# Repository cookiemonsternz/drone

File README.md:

# F<sub>~ish</sub>PV

_Tinywhoop drone with custom ESC, FC, and frame._

## What?

F<sub>\~ish</sub>PV is a open source, custom stack, 75mm tinywhoop drone design.
It utilises AM32 for the ESC firmware and Betaflight for the flight controller. 

Custom components include a from-scratch frame, designed for 3d printing (in HP-12-CF filament), a fully custom 15A ESC, and a custom FC. 

**The ESC:**
- 15A Continuous
- 20A Peak for 5s (unverified :O)
- 2S Battery (only)
- AM32 Firmware
- DSHOT Communication + Voltage telemetry
- Current Sense
  
**The FC:**
- STM32F405
- OSD: MAX7456
- IMU: ICM-42688-P
- 128Mbit blackbox
- USB DFU
- 2S Battery (only)
- BEC: 5V/0.5A Max
- Mounting: 25.5x25.5
- Dimensions: 28.3x28.3x10
- UART: 1, 4, 5
- Buzzer!

## Why?

To be honest a lot of this project was just for my own learning, but I also wanted to make a drone that could be generally cheaper than buying prebuilt components. I've somewhat achieved this, with a net cost of ~$300 USD, but obviously this cost is higher due to lack of bulk pricing. Unfortunately, some parts I wanted to design from scratch proved to be infeasible within the scope of this project (namely vtx and vrx) so that has driven the total cost up slightly.

Aside from that, drones are cool, and tinywhoops especially so. The main benefit in my opinion is the crashability. The size makes it much more feasible to use alternative manufacturing options. As I mentioned earlier, I designed this with HP-12-CF filament in mind, but HP-12 MJF Nylon is also a very feasible option that could potentially be quite durable (I have simulated both, but it is worth noting that the CF simulations will not be entirely accurate due to the weakness along layer lines not being modelled).

## How to use?

The drone assembly should be reasonably straightforward, I have provided a wonderful exploded diagram that should help significantly:

Feel free to assemble it how you see fit, I'll likely change some things in the future but I'd like to try this configuration for now.

For wiring, theres this handy diagram. A lot of it just uses jst-sh connectors (as conformant to the [Betaflight Connector Standard](https://betaflight.com/docs/development/manufacturer/connector-standard)).

The ELRS receiver and vtx module can be attached however you see fit. I have included a mounting plate, and myself intend to use hot glue but velcro, etc. are also options.

Aside from the physical assembly, the FC and ESC must be flashed as outlined below or in the respective folders in **firmware/**. As I didn't want to do a bunch of pull requests for a likely one off design, I have provided compiled versions of the firmware. If you want to compile yourself, check out my forks of [Betaflight](https://github.com/cookiemonsternz/betaflight) and [AM32](https://github.com/cookiemonsternz/AM32). AM32 was built using github actions, and Betaflight was built locally using WSL as outlined in [the documentation](https://betaflight.com/docs/development#development).

### ESC Firmware

The esc runs on AM32, an open source ESC firmware which manages motor control, communication via dshot, and telemetry.

#### Bootloader

First of all, we need to install the bootloader onto each of the chips. For each chip, connect via the exposed swd/io interface, as outlined in the following table, and flash the bootloader hex file from **firmware/esc/bootloader/**

| MCU | SWDIO | SWDCLK |
|-----|-------|--------|
| 1   | TP1   | TP2    |
| 2   | TP3   | TP4    |
| 3   | TP6   | TP5    |
| 4   | TP8   | TP7    |

#### Firmware

Next connect the flight controller (which should be flashed before this step),
visit [am32 configurator](https://am32.ca/) and upload the firmware from **firmware/esc/**

---

### FC Firmware

Installation follows the same procedure as pretty much any flight controller.
Visit [Betaflight Configurator](https://app.betaflight.com/) and select firmware flasher. 

At the bottom of the screen, press load local:

Upload the hex file and then hit flash!

That's it, should be all configured (maybe) but I'd reccomend going through and doing the regular adjustments and calibration.

## Renders

## Zine Page

## Simulations

I ran a handful of simulations in FreeCAD, and these are just a small sample of the results I got. 

First up, a collision where the battery is impacted. Think the drone just dropping onto the ground. This is for a collision at approximately 50km/h assuming a collision time of 25ms and a net mass of around 250g (so probably a bit extreme), to be specific, I modelled a force of 150N.

As you can see, there is even deflection across all four mounting posts for the FC/ESC stack, which will result in minimal tensile strain on the PCBs (which is the typical cause of damage).

Another type of collision I modelled is just a collision directly to the prop guards. Again, a 150N force which would be ~50km/h as mentioned above.

There is a lot of displacement on the prop guard but it is effectively dissipated and won't have much impact on the electronics, which is the main thing to be worried about. 
For this specific impact, I would be reasonably worried about damage to the frame, but for most crashes (which are probably not at 50km/h) it should be perfectly fine.

Many more simulations at different loads and also modelling the HP-12 MJF material can be found [here](https://github.com/cookiemonsternz/drone/blob/main/journals/journal-14-05-2026.md).

## BOM

| Desc                               | Value              | Package        | Link                                                                                        | Num | Needed | MOQ | MOQ Price | Net Price | Running Total |
|------------------------------------|--------------------|----------------|---------------------------------------------------------------------------------------------|-----|--------|-----|-----------|-----------|---------------|
| **Capacitors**                         |                    |                |                                                                                             |     |        |     |           |           |               |
| 10nF Ceramic Cap, 0402             | 10nF               | 0402           | https://www.lcsc.com/product-detail/C15195.html                                             | 1   | 1      | 100 | $0.16     | $0.16     | $0.16         |
| 22nF Ceramic Cap, 0402             | 22nF               | 0402           | https://www.lcsc.com/product-detail/C1532.html                                              | 2   | 2      | 100 | $0.21     | $0.21     | $0.37         |
| 100nF Ceramic Cap, 0402            | 100nF              | 0402           | https://www.lcsc.com/product-detail/C1525.html                                              | 44  | 44     | 100 | $0.15     | $0.15     | $0.52         |
| 1uF Ceramic Cap, 0402              | 1uF                | 0402           | https://www.lcsc.com/product-detail/C52923.html                                             | 4   | 4      | 100 | $0.4      | $0.40     | $0.92         |
| 2.2uF Ceramic Cap, 0402            | 2.2uF              | 0402           | https://www.lcsc.com/product-detail/C12530.html                                             | 3   | 3      | 100 | $0.32     | $0.32     | $1.24         |
| 4.7uF Capacitors, 0603             | 4.7uF              | 0603           | https://www.lcsc.com/product-detail/C19666.html                                             | 4   | 4      | 10  | $0.11     | $0.11     | $1.35         |
| 22uF Capacitors, 0603              | 22uF               | 0603           | https://www.lcsc.com/product-detail/C86295.html                                             | 4   | 4      | 10  | $0.16     | $0.16     | $1.51         |
| 22uF Capacitors, 0805              | 22uF               | 0805           | https://www.lcsc.com/product-detail/C29277.html                                             | 2   | 2      | 10  | $0.21     | $0.21     | $1.72         |
| 22uF Electrolytic Cap, SMD         | 22uF               | SMD,D4xL5.4mm  | https://www.lcsc.com/product-detail/C335975.html                                            | 2   | 2      | 20  | $0.48     | $0.48     | $2.20         |
| 47uF Electrolytic Cap, SMD         | 47uF               | SMD,D4xL5.4mm  | https://www.lcsc.com/product-detail/C87853.html                                             | 2   | 2      | 20  | $0.53     | $0.53     | $2.73         |
| **Resistors**                          |                    |                |                                                                                             |     |        |     |           |           |               |
| 22R Resistors, 0402                | 22r                | 0402           | https://www.lcsc.com/product-detail/C2906914.html                                           | 26  | 26     | 100 | $0.07     | $0.07     | $2.80         |
| 75R Resistor, 0402                 | 75?                | 0402           | https://www.lcsc.com/product-detail/C25133.html                                             | 4   | 4      | 100 | $0.09     | $0.09     | $2.89         |
| 1k Resistor, 0402                  | 1k?                | 0402           | https://www.lcsc.com/product-detail/C11702.html                                             | 17  | 17     | 100 | $0.11     | $0.11     | $3.00         |
| 2.2k Resistor, 0402                | 2.2k?              | 0402           | https://www.lcsc.com/product-detail/C25879.html                                             | 3   | 3      | 100 | $0.10     | $0.10     | $3.10         |
| 10k Resistor, 0402                 | 10k?               | 0402           | https://www.lcsc.com/product-detail/C25744.html                                             | 6   | 6      | 100 | $0.13     | $0.13     | $3.23         |
| 100k Resistor, 0402                | 100k?              | 0402           | https://www.lcsc.com/product-detail/C25741.html                                             | 4   | 4      | 100 | $0.09     | $0.09     | $3.32         |
| 10k Resistor Arrays, 0603x4        | 10k                | 0603x4         | https://www.lcsc.com/product-detail/C110924.html                                            | 6   | 6      | 50  | $0.55     | $0.55     | $3.87         |
| 124k Voltage Div Resistor, 0603    | 124k               | 0603           | https://www.lcsc.com/product-detail/C2933136.html                                           | 1   | 1      | 100 | $0.11     | $0.11     | $3.98         |
| 0.5m Shunt Resistor, 1216          | 0.5mr              | 1216           | https://www.lcsc.com/product-detail/C2688874.html                                           | 1   | 1      | 1   | $1.01     | $1.01     | $4.99         |
| **Diodes**                             |                    |                |                                                                                             |     |        |     |           |           |               |
| Red LED                            |                    | 0603           | https://www.lcsc.com/product-detail/C51933292.html                                          | 1   | 1      | 50  | $0.13     | $0.13     | $5.12         |
| Blue LED                           |                    | 0603           | https://www.lcsc.com/product-detail/C2288.html                                              | 1   | 1      | 50  | $0.51     | $0.51     | $5.63         |
| Green LED                          |                    | 0603           | https://www.lcsc.com/product-detail/C22371297.html                                          | 1   | 1      | 50  | $0.71     | $0.71     | $6.34         |
| Schottky Diode                     |                    | SOD-323        | https://www.lcsc.com/product-detail/C191023.html                                            | 2   | 2      | 50  | $0.54     | $0.54     | $6.88         |
| **Connectors**                         |                    |                |                                                                                             |     |        |     |           |           |               |
| Camera Conn                        | 3P SH              | SMD,P=1mm      | https://www.lcsc.com/product-detail/C7430452.html                                           | 1   | 1      | 5   | $0.34     | $0.34     | $7.22         |
| UART Conns                         | 4P SH              | SMD,P=1mm      | https://www.lcsc.com/product-detail/C7433440.html                                           | 3   | 3      | 10  | $0.35     | $0.35     | $7.57         |
| VTX Conn                           | 5P SH              | SMD,P=1mm      | https://www.lcsc.com/product-detail/C2845373.html                                           | 1   | 1      | 5   | $0.58     | $0.58     | $8.15         |
| ESC Conns                          | 8P SH              | SMD,P=1mm      | https://www.lcsc.com/product-detail/C2764202.html                                           | 2   | 2      | 5   | $0.61     | $0.61     | $8.76         |
| USB Micro B Conn                   |                    | SMD            | https://www.lcsc.com/product-detail/C404969.html                                            | 1   | 1      | 10  | $0.41     | $0.41     | $9.17         |
| **FC**                                 |                    |                |                                                                                             |     |        |     |           |           |               |
| STM32F405 (U1)                     |                    | LQFP-64(10x10) | https://www.lcsc.com/product-detail/C15742.html                                             | 1   | 1      | 1   | $3.93     | $3.93     | $13.10        |
| ICM-42668-P : IMU (U2)             |                    | LGA-14(2.5x3)  | https://www.lcsc.com/product-detail/C1850418.html                                           | 1   | 1      | 1   | $12.88    | $12.88    | $25.98        |
| MAX-7456eui+ (U3)                  | Source: Aliexpress |                | https://www.aliexpress.com/item/33005990891.html                                            | 1   | 1      | 1   | $4.28     | $4.28     | $30.26        |
| BL8072CLTR-3.3 (3.3V LDO) (U6)     | 3.3V               | SOT-223-3      | https://www.lcsc.com/product-detail/C843780.html                                            | 1   | 1      | 5   | $0.99     | $0.99     | $31.25        |
| SGM2212-3.3XKC3G/TR (IMU LDO) (U7) | 3.3V               | SOT-223-3      | https://www.lcsc.com/product-detail/C3294699.html                                           | 1   | 1      | 1   | $0.61     | $0.61     | $31.86        |
| W25Q128JVSIQ TR (Flash) (U8)       |                    | SOIC-8-208mil  | https://www.lcsc.com/product-detail/C97521.html                                             | 1   | 1      | 1   | $2.32     | $2.32     | $34.18        |
| TPS62173DSG (5V BEC) (U4, U5)      | 5V                 | WSON-8-EP(2x2) | https://www.lcsc.com/product-detail/C181384.html                                            | 2   | 2      | 1   | $0.93     | $1.86     | $36.04        |
| BMP280 Baro (U10)                  |                    | LGA-8(2x2.5)   | https://www.lcsc.com/product-detail/C83291.html                                             | 1   | 1      | 1   | $6.90     | $6.90     | $42.94        |
| 27MHz Crystal (Y1)                 | 27MHz              | SMD3225-4P     | https://www.lcsc.com/product-detail/C9008.html                                              | 1   | 1      | 10  | $0.77     | $0.77     | $43.71        |
| 8MHz Crystal w/ Caps (Y2)          | 8MHz               | SMD3213-3P     | https://www.lcsc.com/product-detail/C907975.html                                            | 1   | 1      | 5   | $1.05     | $1.05     | $44.76        |
| BEC Inductors (L1, L2)             | 2.2uH              | 0806           | https://www.lcsc.com/product-detail/C695610.html                                            | 1   | 1      | 5   | $0.82     | $0.82     | $45.58        |
| BOOT Button (SW2)                  |                    | SMD,4x3mm      | https://www.lcsc.com/product-detail/C720477.html                                            | 1   | 1      | 10  | $0.54     | $0.54     | $46.12        |
| Reverse Pol. Mosfet (Q1)           |                    | SOT-23         | https://www.lcsc.com/product-detail/C15127.html                                             | 1   | 1      | 10  | $0.59     | $0.59     | $46.71        |
| **ESC**                                |                    |                |                                                                                             |     |        |     |           |           |               |
| 470nH Inductor, 0603               | 470nH              | 0603           | https://www.lcsc.com/product-detail/C113132.html                                            | 1   | 1      | 10  | $0.47     | $0.47     | $47.18        |
| Mosfets (SP40N03GNJ)               |                    | PDFN-8L(3x3)   | https://www.lcsc.com/product-detail/C22466709.html                                          | 24  | 24     | 5   | $1.05     | $5.25     | $52.43        |
| ESC MCUs (AT32F421G8U7)            |                    | QFN-28-EP(4x4) | https://www.lcsc.com/product-detail/C2765098.html                                           | 4   | 4      | 1   | $0.85     | $3.40     | $55.83        |
| ESC Mosfet Gate Drivers (NSG2065Q) |                    | QFN-24-EP(4x4) | https://www.lcsc.com/product-detail/C41414478.html                                          | 4   | 4      | 1   | $0.48     | $1.92     | $57.75        |
| Current Sense Amplifier (INA180B2) |                    | SOT-23-5       | https://www.lcsc.com/product-detail/C2057844.html                                           | 1   | 1      | 1   | $0.26     | $0.26     | $58.01        |
| 8V Regulator (LMR51420YDDCR)       |                    | SOT-23-6       | https://www.lcsc.com/product-detail/C5383002.html                                           | 1   | 1      | 1   | $0.83     | $0.83     | $58.84        |
| 3.3V Regulator (TLV76733DRVR)      |                    | WSON-6(2x2)    | https://www.lcsc.com/product-detail/C2848334.html                                           | 1   | 1      | 5   | $1.01     | $1.01     | $59.85        |
| **BOARDS**                             |                    |                |                                                                                             |     |        |     |           |           | $59.85        |
| ESC Board + Stencil (JLCPCB)       |                    |                |                                                                                             |     |        |     |           | $5.29     | $65.14        |
| FC Board + Stencil (JLCPCB)        |                    |                |                                                                                             |     |        |     |           | $5.21     | $70.35        |
| Frame (JLC3DP, HP-12-CF)           |                    |                |                                                                                             |     |        |     |           | $5.56     | $75.91        |
| **MODULES**                            |                    |                |                                                                                             |     |        |     |           |           | $75.91        |
| ELRS Receiver (RP1 Nano Clone)     |                    |                | https://www.aliexpress.com/item/1005005236594556.html                                       | 1   | 1      | 1   | $12.62    | $12.62    | $88.53        |
| CaddX Ant Camera                   |                    |                | https://www.aliexpress.com/item/1005008798090166.html                                       | 1   | 0      | 1   | $12.99    | $0.00     | $88.53        |
| PandaRC Nano25 VTX                 |                    |                | https://www.aliexpress.com/item/1005011701933149.html                                       | 1   | 0      | 1   | $18.94    | $0.00     | $88.53        |
| Happymodel RS1102 13500KV Motors   |                    |                | https://kiwiquads.co.nz/product/happymodel-rs1102-kv13500-brushless-motor-for-m8-freestyle/ | 4   | 4      | 4   | $11.11    | $44.44    | $132.97       |
| 40mm 1.5mm Shaft Triblade Props    |                    |                | https://www.aliexpress.com/item/1005010520091463.html                                       | 4   | 4      | 16  | $6.37     | $6.37     | $139.34       |
| 2s 680mah lipo                     |                    |                | https://kiwiquads.co.nz/product/betafpv-lava-series-ii-2s-680mah-95c/                       | 1   | 1      | 1   | $14.62    | $14.62    | $153.96       |
| Radiomaster T8L                    |                    |                | https://radiomasterrc.com/products/t8l-radio-controller?variant=47089026465984              | 1   | 1      | 1   | $34.99    | $34.99    | $188.95       |
| TS832 Receiver                     |                    |                | https://www.aliexpress.com/item/1005012037139433.html                                       | 1   | 0      | 1   | $43.86    | $0.00     | $188.95       |

| Totals (EXCL. VIDEO SYSTEM) |         |             |
|-----------------------------|---------|-------------|
| Vendor                      | Net     | W/ Shipping |
| JLCPCB / 3DP                | $16.06  | $41.99      |
| LCSC                        | $55.16  | $55.55      |
| Aliexpress                  | $23.27  | $22.95      |
| Kiwiquads                   | $59.05  | $61.96      |
| Radiomaster                 | $34.99  | $44.99      |
| JLCPCB                      | $10.50  | $32.06      |
| ---                         | $199.03 | $259.50     |

## Cad Links

All of the CAD source files can be found on [Onshape](https://cad.onshape.com/documents/5b69b7ad5dc2bcb1a562cae6/w/28cfd389aaff8b3000581458/e/21531bda6c88e5e5db7731e6?configuration=List_q74UD91e5eSlmt%3DDefault&renderMode=0&uiState=6a005b50d3c7c0f6100b1ec5). 
The physics simulations can be found in the FreeCAD project under **hardware/cad/sim/**

## Directory Structure

- **firmware/**
  - **esc/** - ESC Firmware (AM32)
  - **fc/** - FC Firmware (Betaflight)
- **hardware/**
    - **bom/** - BOM Files (CSV and LibreOffice Calc)
    - **cad/** - CAD Files
      - **render/** - Files for rendering (inc. gltf models) *Note that the Blender file for the renders exceeds the maximum file size for Github, it can be found in [Google Drive](https://drive.google.com/file/d/1S7Jwgq-ZpHFBb5yz26d0MQlCH4Twi4XQ/view?usp=sharing).*
      - **sim/** - FreeCAD files for FEM Analysis
    - **esc/** - ESC KiCad Project
      - **production/** - Production files (Gerber, etc.)
    - **fc/** - FC KiCad Project
      - **production/** - Production files (Gerber, etc.)
    - **lib/** - Shared KiCad libraries
    - **wiring-diagram/** - Wiring diagram
- **journals/**
- **zine/** - Zine page :)

## References
[Betaflight Documentation](https://betaflight.com/docs/development)

[AM32 Documentation](https://wiki.am32.ca/general/docs.html) - Especially re [Hardware Design](https://wiki.am32.ca/development/Hardware-Design.html)

[AcciFPV FC](https://www.pcbway.com/project/shareproject/Acci_FPV_Flight_Controller_Betaflight_STM32F405_AT32F435_48fb0ecb.html)

[Hack Club Blueprint - FC Guided Project](https://blueprint.hackclub.com/starter-projects/flightcontroller)

[JustFPV ESC Design](https://www.youtube.com/watch?v=TwAmmPxOpTM)

AM32 & Betaflight Discords

And various others which I have forgotten.

#### This project was created for [Hack Club](https://hackclub.com/) - [Fallout](https://fallout.hackclub.com/)

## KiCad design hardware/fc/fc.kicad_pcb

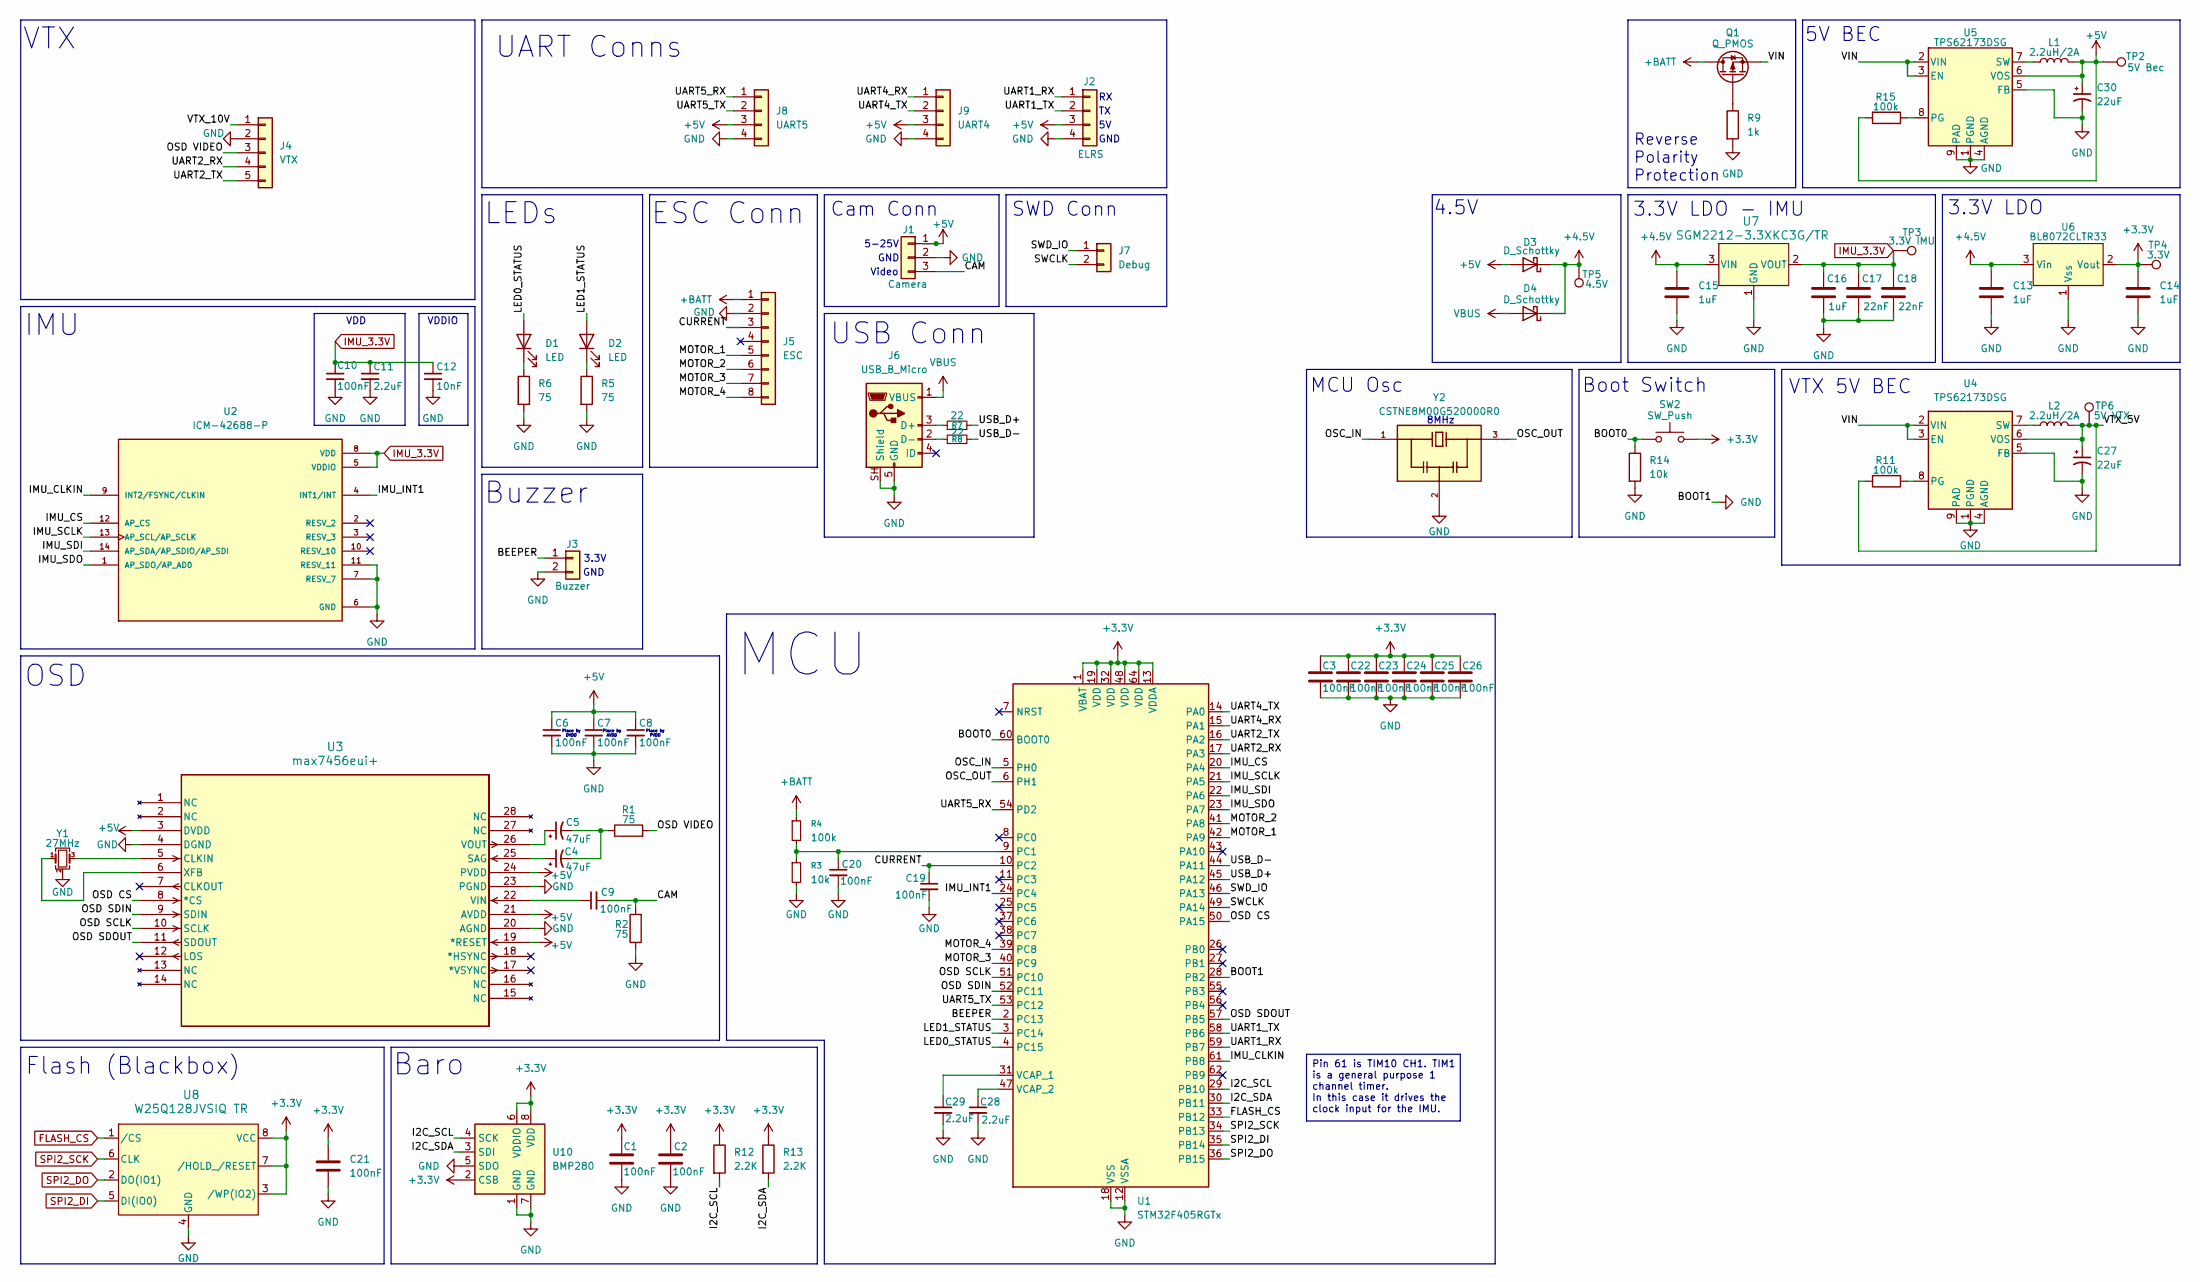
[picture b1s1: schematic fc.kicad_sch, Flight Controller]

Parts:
C1, C2, C3, C6, C7, C8, C9, C10, C19, C20, C21, C22, C23, C24, C25, C26: 100nF; C_0402_1005Metric
C4, C5: 47uF; CP_Elec_4x5.4
C11, C28, C29: 2.2uF; C_0402_1005Metric
C12: 10nF; C_0402_1005Metric
C13, C14, C15, C16: 1uF; C_0402_1005Metric
C17, C18: 22nF; C_0402_1005Metric
C27, C30: 22uF; CP_Elec_4x5.4
D1, D2: LED; LED_0603_1608Metric
D3, D4: D_Schottky; D_SOD-323
J1: Camera; JST_SH_BM03B-SRSS-TB_1x03-1MP_P1.00mm_Vertical
J2: ELRS; JST_SH_BM04B-SRSS-TB_1x04-1MP_P1.00mm_Vertical
J3: Buzzer; SolderWire-0.1sqmm_1x02_P3.6mm_D0.4mm_OD1mm
J4: VTX; JST_SH_BM05B-SRSS-TB_1x05-1MP_P1.00mm_Vertical
J5: ESC; JST_SH_BM08B-SRSS-TB_1x08-1MP_P1.00mm_Vertical
J6: USB_B_Micro; SHOUHAN_MICROXNJ
J7: Debug; SolderWire-0.1sqmm_1x02_P3.6mm_D0.4mm_OD1mm
J8: UART5; JST_SH_BM04B-SRSS-TB_1x04-1MP_P1.00mm_Vertical
J9: UART4; JST_SH_BM04B-SRSS-TB_1x04-1MP_P1.00mm_Vertical
L1, L2: 2.2uH/2A; INDC1608X95N
Q1: Q_PMOS; SOT-23
R1, R2, R5, R6: 75; R_0402_1005Metric
R3, R14: 10k; R_0402_1005Metric
R4, R11, R15: 100k; R_0402_1005Metric
R7, R8: 22; R_0402_1005Metric
R9: 1k; R_0402_1005Metric
R12, R13: 2.2K; R_0402_1005Metric
SW2: SW_Push; SW_TS-1088-AR02016
TP2: 5V Bec; TestPoint_Pad_D1.0mm
TP3: 3.3V IMU; TestPoint_Pad_D1.0mm
TP4: 3.3V; TestPoint_Pad_D1.0mm
TP5: 4.5V; TestPoint_Pad_D1.0mm
TP6: 5V VTX; TestPoint_Pad_D1.0mm
U1: STM32F405RGTx; LQFP-64_10x10mm_P0.5mm
U2: ICM-42688-P; PQFN50P300X250X97-14N; PARTREV 1.2
U3: max7456eui+; 21-0108G_U28E-5_MXM
U4, U5: TPS62173DSG; WSON-8-1EP_2x2mm_P0.5mm_EP0.9x1.6mm_ThermalVias
U6: BL8072CLTR33; SOT-223-3_TabPin2
U7: SGM2212-3.3XKC3G/TR; SOT-223-3_TabPin2
U8: W25Q128JVSIQ TR; SOIC_208MIL_WIN
U10: BMP280; Bosch_LGA-8_2x2.5mm_P0.65mm_ClockwisePinNumbering
Y1: 27MHz; Crystal_SMD_3225-4Pin_3.2x2.5mm
Y2: CSTNE8M00G520000R0; OSC_CSTNE8M00G520000R0; PARTREV JGC42-8858A

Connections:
+3.3V: C1.1, C2.1, C3.1, C14.1, C21.1, C22.1, C23.1, C24.1, C25.1, C26.1, R12.1, R13.1, SW2.2, TP4.1, U1.1 (VBAT), U1.13 (VDDA), U1.19 (VDD), U1.32 (VDD), U1.48 (VDD), U1.64 (VDD), U6.2 (Vout), U8.3 (/WP(IO2)), U8.7 (/HOLD_/RESET), U8.8 (VCC), U10.2 (CSB), U10.6 (VDDIO), U10.8 (VDD); also elsewhere on the board
+4.5V: C13.1, C15.1, D3.1 (K), D4.1 (K), TP5.1 (1_1), U6.3 (Vin), U7.3 (VIN)
+5V: C6.1, C7.1, C8.1, C30.1, D3.2 (A), J1.1, J2.3, J8.3, J9.3, L1.2, R15.2, TP2.1, U3.3 (DVDD), U3.19 (*RESET), U3.21 (AVDD), U3.24 (PVDD), U5.6 (VOS); also elsewhere on the board
+BATT: J5.1, Q1.D, R4.1
/BEEPER: J3.1, U1.2 (PC13)
/BOOT0: R14.1, SW2.1, U1.60 (BOOT0)
/CAM: C9.2, J1.3, R2.2
/CURRENT: C19.1, J5.3, U1.10 (PC2)
/I2C_SCL: R12.2, U1.29 (PB10), U10.4 (SCK)
/I2C_SDA: R13.2, U1.30 (PB11), U10.3 (SDI)
/IMU_CLKIN: U1.61 (PB8), U2.9 (INT2/FSYNC/CLKIN)
/IMU_CS: U1.20 (PA4), U2.12 (AP_CS)
/IMU_INT1: U1.24 (PC4), U2.4 (INT1/INT)
/IMU_SCLK: U1.21 (PA5), U2.13 (AP_SCL/AP_SCLK)
/IMU_SDI: U1.22 (PA6), U2.14 (AP_SDA/AP_SDIO/AP_SDI)
/IMU_SDO: U1.23 (PA7), U2.1 (AP_SDO/AP_AD0)
/LED0_STATUS: D1.2 (A), U1.4 (PC15)
/LED1_STATUS: D2.2 (A), U1.3 (PC14)
/MOTOR_1: J5.5, U1.42 (PA9)
/MOTOR_2: J5.6, U1.41 (PA8)
/MOTOR_3: J5.7, U1.40 (PC9)
/MOTOR_4: J5.8, U1.39 (PC8)
/OSC_IN: U1.5 (PH0), Y2.1
/OSC_OUT: U1.6 (PH1), Y2.3
/OSD CS: U1.50 (PA15), U3.8 (*CS)
/OSD SCLK: U1.51 (PC10), U3.10 (SCLK)
/OSD SDIN: U1.52 (PC11), U3.9 (SDIN)
/OSD SDOUT: U1.57 (PB5), U3.11 (SDOUT)
/OSD VIDEO: J4.3, R1.2
/SWCLK: J7.2, U1.49 (PA14)
/SWD_IO: J7.1, U1.46 (PA13)
/UART1_RX: J2.1, U1.59 (PB7)
/UART1_TX: J2.2, U1.58 (PB6)
/UART2_RX: J4.4, U1.17 (PA3)
/UART2_TX: J4.5, U1.16 (PA2)
/UART4_RX: J9.1, U1.15 (PA1)
/UART4_TX: J9.2, U1.14 (PA0)
/UART5_RX: J8.1, U1.54 (PD2)
/UART5_TX: J8.2, U1.53 (PC12)
/USB_D+: R7.2, U1.45 (PA12)
/USB_D-: R8.2, U1.44 (PA11)
/VIN: Q1.S, U4.2 (VIN), U4.3 (EN), U5.2 (VIN), U5.3 (EN)
/VTX_5V: C27.1, L2.2, R11.2, TP6.1, U4.6 (VOS); also elsewhere on the board
/VTX_10V: J4.1
FLASH_CS: U1.33 (PB12), U8.1 (/CS)
GND: C1.2, C2.2, C3.2, C6.2, C7.2, C8.2, C10.2, C11.2, C12.2, C13.2, C14.2, C15.2, C16.2, C17.2, C18.2, C19.2, C20.2, C21.2, C22.2, C23.2, C24.2, C25.2, C26.2, C27.2, C28.2, C29.2, C30.2, J1.2, J2.4, J3.2, J4.2, J5.2, J6.5 (GND), J6.S3, J6.S4, J6.S5, J6.S6, J6.SH (Shield), J8.4, J9.4, R2.1, R3.2, R5.2, R6.2, R9.2, R14.2, U1.12 (VSSA), U1.18 (VSS), U1.28 (PB2), U1.63 (VSS), U2.6 (GND), U2.7 (RESV_7), U2.11 (RESV_11), U3.4 (DGND), U3.20 (AGND), U3.23 (PGND), U4.1 (PGND), U4.4 (AGND), U4.5 (FB), U4.9 (PAD), U5.1 (PGND), U5.4 (AGND), U5.5 (FB), U5.9 (PAD), U6.1 (Vss), U7.1 (GND), U8.4 (GND), U10.1 (GND), U10.5 (SDO), U10.7 (GND), Y1.2 (G), Y1.4 (G), Y2.2
IMU_3.3V: C10.1, C11.1, C12.1, C16.1, C17.1, C18.1, TP3.1, U2.5 (VDDIO), U2.8 (VDD), U7.2 (VOUT); also elsewhere on the board
unnamed: C4.2, C5.2, R1.1
unnamed: D1.1 (K), R6.1
unnamed: D2.1 (K), R5.1
unnamed: J6.3 (D+), R7.1
unnamed: J6.2 (D-), R8.1
unnamed: Q1.G, R9.1
unnamed: C20.1, R3.1, R4.2, U1.9 (PC1)
unnamed: C29.1, U1.31 (VCAP_1)
unnamed: C28.1, U1.47 (VCAP_2)
unnamed: U3.5 (CLKIN), Y1.3
unnamed: C4.1, U3.25 (SAG)
unnamed: C9.1, U3.22 (VIN)
unnamed: C5.1, U3.26 (VOUT)
unnamed: U3.6 (XFB), Y1.1
unnamed: R11.1, U4.8 (PG)
unnamed: L2.1, U4.7 (SW)
unnamed: R15.1, U5.8 (PG)
unnamed: L1.1, U5.7 (SW)
SPI2_DI: U1.35 (PB14), U8.5 (DI(IO0))
SPI2_DO: U1.36 (PB15), U8.2 (DO(IO1))
SPI2_SCK: U1.34 (PB13), U8.6 (CLK)
VBUS: D4.2 (A), J6.1 (VBUS)

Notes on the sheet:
ESC Conn
GND
8MHz
Reverse Polarity Protection
VDD
VTX
Place by DVDD
5-25V
USB Conn
Flash (Blackbox)
Place by AVDD
Cam Conn
Baro
3.3V LDO - IMU
SWD Conn
OSD
Boot Switch
UART Conns
VTX 5V BEC
3.3V
5V BEC
Buzzer
IMU
4.5V
MCU
GND
VDDIO
MCU Osc
LEDs
3.3V LDO
Video
Place by PVDD
Pin 61 is TIM10 CH1. TIM1 is a general purpose 1 channel timer. In this case it drives the clock input for the IMU.

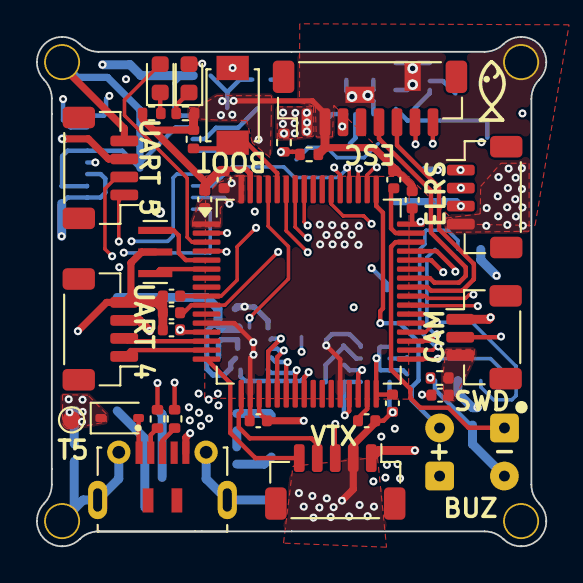
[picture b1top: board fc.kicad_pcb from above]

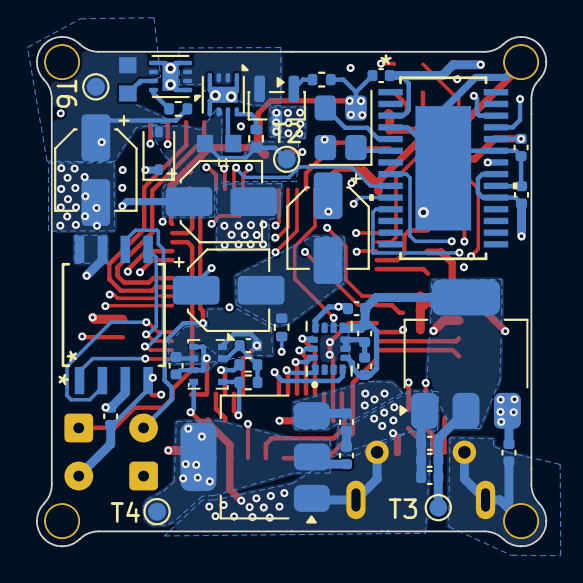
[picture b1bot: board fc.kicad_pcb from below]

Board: 6 copper layers, 28.3 x 28.3 mm, 77 parts (42 on the bottom side), 68 nets.

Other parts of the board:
T2: 5V Bec; TestPoint_Pad_D1.0mm
T3: 3.3V IMU; TestPoint_Pad_D1.0mm
T4: 3.3V; TestPoint_Pad_D1.0mm
T6: 5V VTX; TestPoint_Pad_D1.0mm

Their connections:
+3.3V: T4.1 (1_1); also elsewhere on the board
+5V: T2.1 (1_1); also elsewhere on the board
/VTX_5V: T6.1 (1_1); also elsewhere on the board
IMU_3.3V: T3.1 (1_1); also elsewhere on the board

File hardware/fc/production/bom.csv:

Designator,Footprint,Quantity,Value,LCSC Part #
"C1, C10, C19, C2, C20, C21, C22, C23, C24, C25, C26, C3, C6, C7, C8, C9",0402,16,100nF,
"C11, C28, C29",0402,3,2.2uF,
C12,0402,1,10nF,
"C13, C14, C15, C16",0402,4,1uF,
"C17, C18",0402,2,22nF,
"C27, C30",CP_Elec_4x5.4,2,22uF,
"C4, C5",CP_Elec_4x5.4,2,47uF,
"D1, D2",0603,2,LED,
"D3, D4",D_SOD-323,2,D_Schottky,
J1,JST_SH_BM03B-SRSS-TB_1x03-1MP_P1.00mm_Vertical,1,Camera,
J2,JST_SH_BM04B-SRSS-TB_1x04-1MP_P1.00mm_Vertical,1,ELRS,
J3,SolderWire-0.1sqmm_1x02_P3.6mm_D0.4mm_OD1mm,1,Buzzer,
J4,JST_SH_BM05B-SRSS-TB_1x05-1MP_P1.00mm_Vertical,1,VTX,
J5,JST_SH_BM08B-SRSS-TB_1x08-1MP_P1.00mm_Vertical,1,ESC,
J6,SHOUHAN_MICROXNJ,1,USB_B_Micro,
J7,SolderWire-0.1sqmm_1x02_P3.6mm_D0.4mm_OD1mm,1,Debug,
J8,JST_SH_BM04B-SRSS-TB_1x04-1MP_P1.00mm_Vertical,1,UART5,
J9,JST_SH_BM04B-SRSS-TB_1x04-1MP_P1.00mm_Vertical,1,UART4,
"L1, L2",INDC1608X95N,2,2.2uH/2A,
Q1,SOT-23,1,Q_PMOS,
"R1, R2, R5, R6",0402,4,75,
"R11, R15, R4",0402,3,100k,
"R12, R13",0402,2,2.2K,
"R14, R3",0402,2,10k,
"R7, R8",0402,2,22,
R9,0402,1,1k,
SW2,SW_TS-1088-AR02016,1,SW_Push,
T2,TestPoint_Pad_D1.0mm,1,5V Bec,
T3,TestPoint_Pad_D1.0mm,1,3.3V IMU,
T4,TestPoint_Pad_D1.0mm,1,3.3V,
T6,TestPoint_Pad_D1.0mm,1,5V VTX,
TP5,TestPoint_Pad_D1.0mm,1,4.5V,
U1,LQFP-64_10x10mm_P0.5mm,1,STM32F405RGTx,
U10,Bosch_LGA-8_2x2.5mm_P0.65mm_ClockwisePinNumbering,1,BMP280,
U2,PQFN50P300X250X97-14N,1,ICM-42688-P,
U3,21-0108G_U28E-5_MXM,1,max7456eui+,
"U4, U5",WSON-8-1EP_2x2mm_P0.5mm_EP0.9x1.6mm_ThermalVias,2,TPS62173DSG,
U6,SOT-223-3_TabPin2,1,BL8072CLTR33,
U7,SOT-223-3_TabPin2,1,SGM2212-3.3XKC3G/TR,
U8,SOIC_208MIL_WIN,1,W25Q128JVSIQ TR,
Y1,Crystal_SMD_3225-4Pin_3.2x2.5mm,1,27MHz,
Y2,OSC_CSTNE8M00G520000R0,1,CSTNE8M00G520000R0,

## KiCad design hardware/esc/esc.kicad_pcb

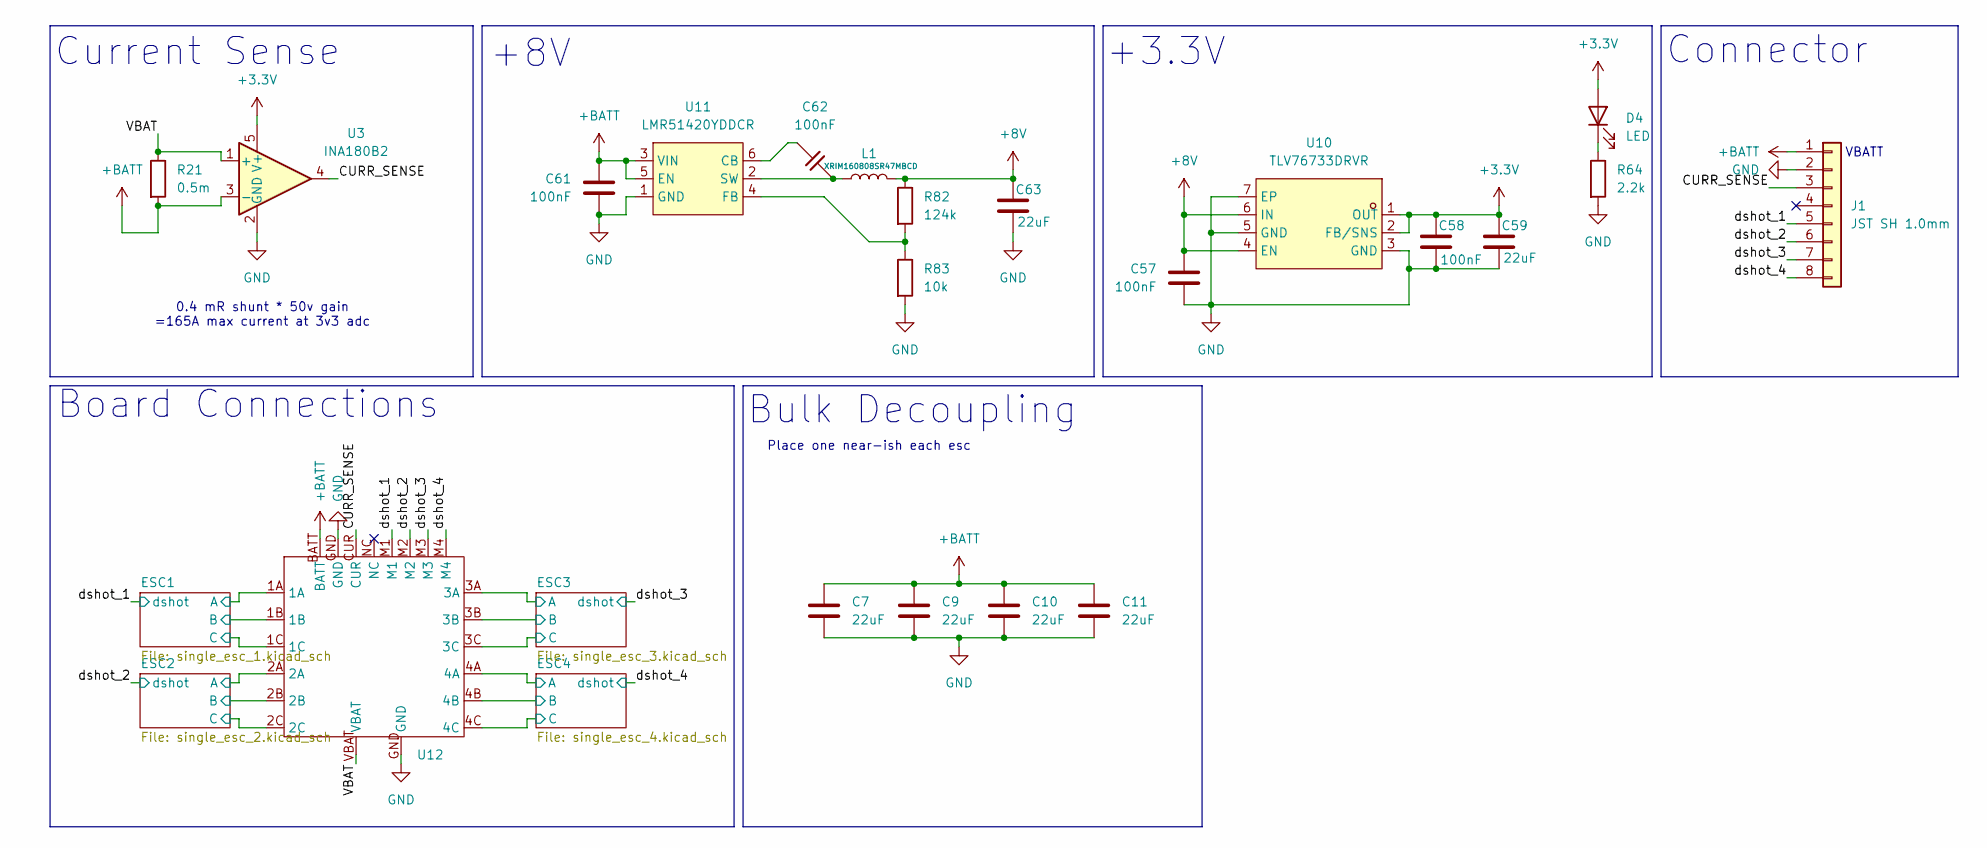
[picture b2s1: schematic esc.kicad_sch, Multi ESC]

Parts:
C7, C9, C10, C11: 22uF; C_0603_1608Metric
C57, C58, C61, C62: 100nF; C_0402_1005Metric
C59, C63: 22uF; C_0805_2012Metric
D4: LED; LED_0603_1608Metric
J1: JST SH 1.0mm; JST_SM08B-SRSS-TB_LF__SN_
L1: XRIM160808SR47MBCD; L_0603_1608Metric
R21: 0.5m; BVNZR000510
R64: 2.2k; R_0402_1005Metric
R82: 124k; R_0603_1608Metric
R83: 10k; R_0402_1005Metric
U3: INA180B2; SOT-23-5
U10: TLV76733DRVR; WSON-6_L2.0-W2.0-P0.65-TL-EP; LCSC Part C2848334
U11: LMR51420YDDCR; SOT-23-6_L2.9-W1.6-P0.95-LS2.9-BL; LCSC Part C5383002
U12: BoardPlate

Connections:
+3.3V: C58.2, C59.2, D4.2 (A), U3.5 (V+), U10.1 (OUT), U10.2 (FB/SNS); also elsewhere on the board
+8V: C57.1, C63.2, L1.2, R82.1, U10.4 (EN), U10.6 (IN); also elsewhere on the board
+BATT: C7.1, C9.1, C10.1, C11.1, C61.1, J1.1, R21.2, U3.3 (-), U11.3 (VIN), U11.5 (EN), U12.BATT; also elsewhere on the board
/CURR_SENSE: J1.3, U3.4, U12.CUR
/ESC1/FloatA: U12.1A; also elsewhere on the board
/ESC1/FloatB: U12.1B; also elsewhere on the board
/ESC1/FloatC: U12.1C; also elsewhere on the board
/ESC2/FloatA: U12.2A; also elsewhere on the board
/ESC2/FloatB: U12.2B; also elsewhere on the board
/ESC2/FloatC: U12.2C; also elsewhere on the board
/ESC3/FloatA: U12.3A; also elsewhere on the board
/ESC3/FloatB: U12.3B; also elsewhere on the board
/ESC3/FloatC: U12.3C; also elsewhere on the board
/ESC4/FloatA: U12.4A; also elsewhere on the board
/ESC4/FloatB: U12.4B; also elsewhere on the board
/ESC4/FloatC: U12.4C; also elsewhere on the board
/VBAT: R21.1, U3.1 (+), U12.VBAT
/dshot_1: J1.5, U12.M1; also elsewhere on the board
/dshot_2: J1.6, U12.M2; also elsewhere on the board
/dshot_3: J1.7, U12.M3; also elsewhere on the board
/dshot_4: J1.8, U12.M4; also elsewhere on the board
GND: C7.2, C9.2, C10.2, C11.2, C57.2, C58.1, C59.1, C61.2, C63.1, J1.2, R64.2, R83.2, U3.2 (GND), U10.3 (GND), U10.5 (GND), U10.7 (EP), U11.1 (GND), U12.GND; also elsewhere on the board
unnamed: D4.1 (K), R64.1
unnamed: C62.2, U11.6 (CB)
unnamed: R82.2, R83.1, U11.4 (FB)
unnamed: C62.1, L1.1, U11.2 (SW)

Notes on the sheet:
+8V
0.4 mR shunt * 50v gain =165A max current at 3v3 adc
Connector
Current Sense
VBATT
Bulk Decoupling
+3.3V
Place one near-ish each esc
Board Connections

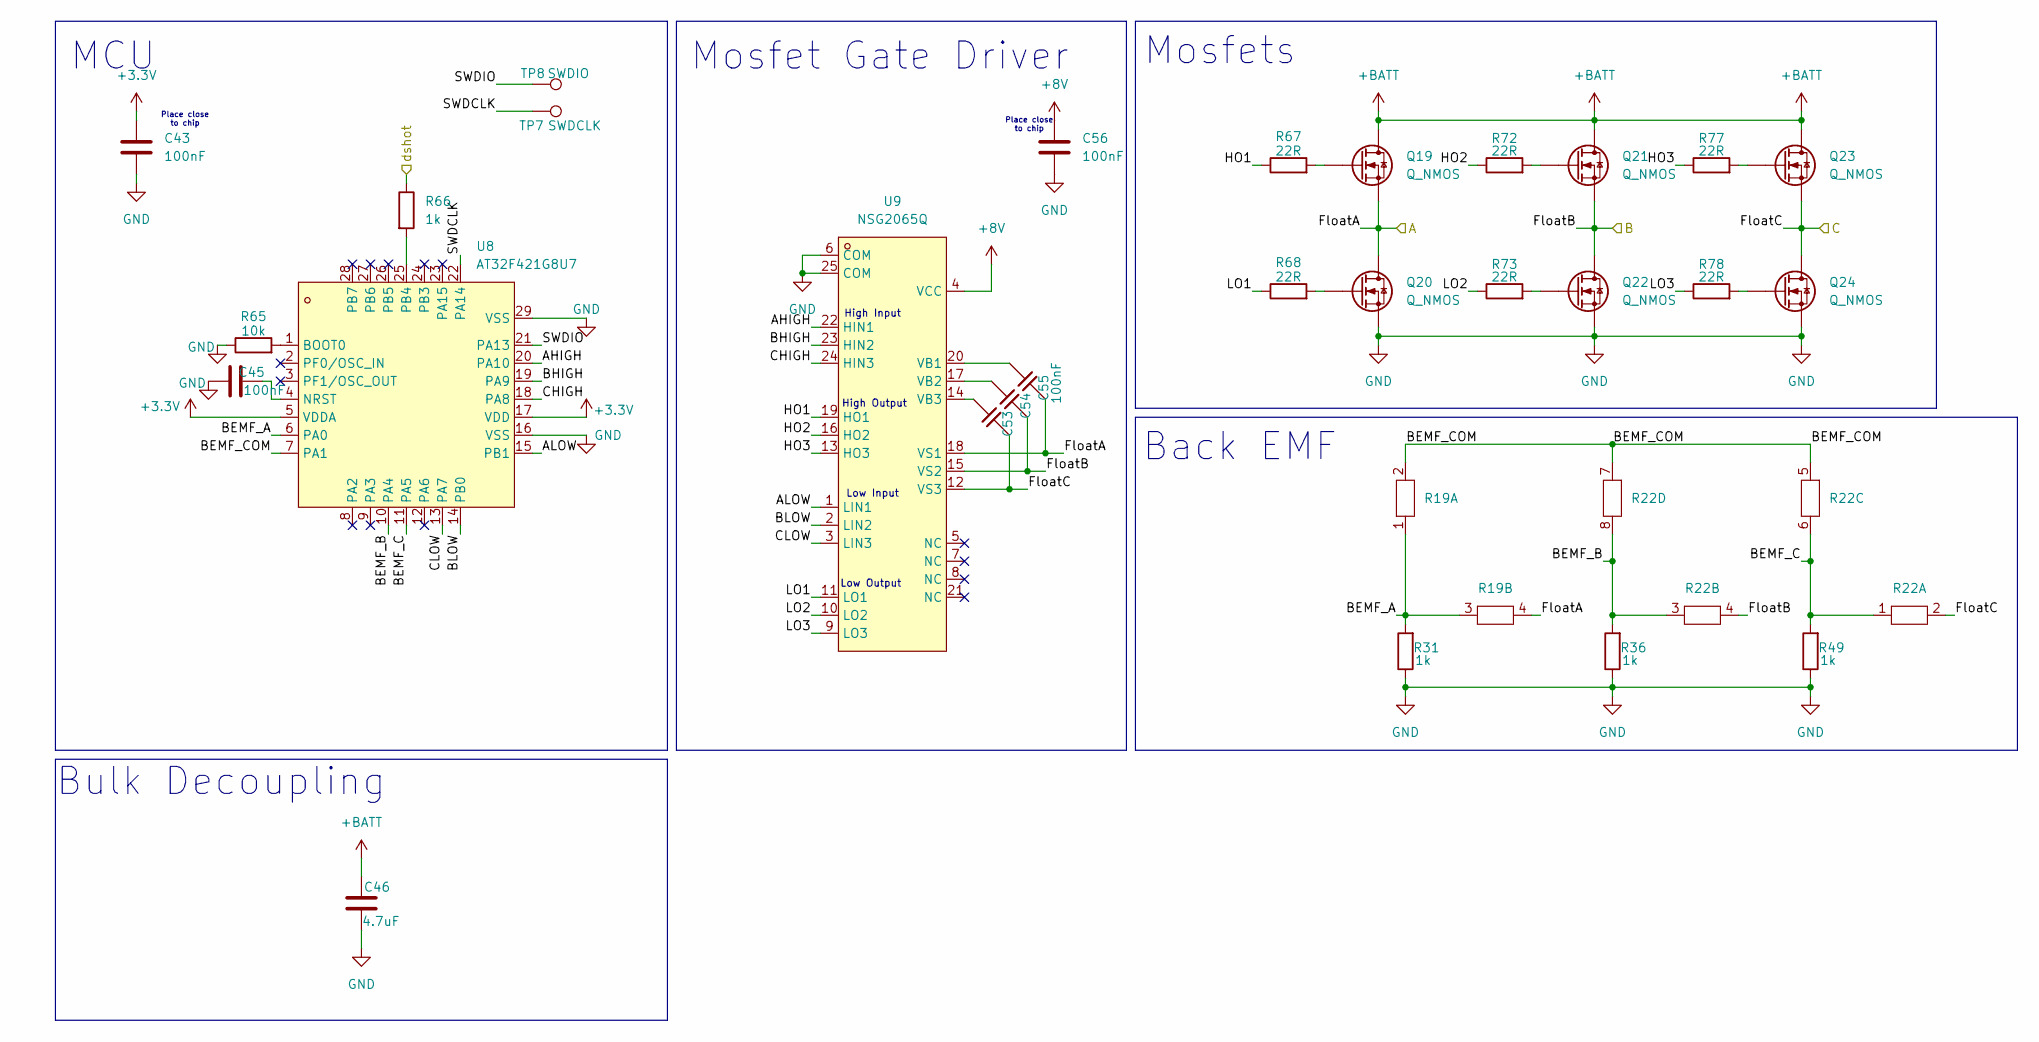
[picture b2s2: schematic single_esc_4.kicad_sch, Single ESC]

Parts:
C43, C45, C53, C54, C55, C56: 100nF; C_0402_1005Metric
C46: 4.7uF; C_0603_1608Metric
Q19, Q20, Q21, Q22, Q23, Q24: Q_NMOS; POWERPAK-1212-8_L3.0-W3.0-P0.65-LS3.3-BL
R19, R22: RES_4D03_0603_3P2X1P6_ROH
R31, R36, R49, R66: 1k; R_0402_1005Metric
R65: 10k; R_0402_1005Metric
R67, R68, R72, R73, R77, R78: 22R; R_0402_1005Metric
TP7: SWDCLK; TestPoint_Pad_D1.0mm
TP8: SWDIO; TestPoint_Pad_D1.0mm
U8: AT32F421G8U7; QFN-28_L4.0-W4.0-P0.40-TL-EP2.4; LCSC Part C2765098
U9: NSG2065Q; QFN-24_L4.0-W4.0-P0.50-TL-EP2.8; LCSC Part C41414478

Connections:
+3.3V: C43.1, U8.5 (VDDA), U8.17 (VDD); also elsewhere on the board
+8V: C56.1, U9.4 (VCC); also elsewhere on the board
+BATT: C46.1, Q19.D, Q21.D, Q23.D; also elsewhere on the board
/ESC4/AHIGH: U8.20 (PA10), U9.22 (HIN1)
/ESC4/ALOW: U8.15 (PB1), U9.1 (LIN1)
/ESC4/BEMF_A: R19.1, R19.3, R31.2, U8.6 (PA0)
/ESC4/BEMF_B: R22.3, R22.8, R36.2, U8.10 (PA4)
/ESC4/BEMF_C: R22.1, R22.6, R49.2, U8.11 (PA5)
/ESC4/BEMF_COM: R19.2, R22.5, R22.7, U8.7 (PA1)
/ESC4/BHIGH: U8.19 (PA9), U9.23 (HIN2)
/ESC4/BLOW: U8.14 (PB0), U9.2 (LIN2)
/ESC4/CHIGH: U8.18 (PA8), U9.24 (HIN3)
/ESC4/CLOW: U8.13 (PA7), U9.3 (LIN3)
/ESC4/FloatA: C55.1, Q19.S, Q20.D, R19.4, U9.18 (VS1); also elsewhere on the board
/ESC4/FloatB: C54.1, Q21.S, Q22.D, R22.4, U9.15 (VS2); also elsewhere on the board
/ESC4/FloatC: C53.1, Q23.S, Q24.D, R22.2, U9.12 (VS3); also elsewhere on the board
/ESC4/HO1: R67.1, U9.19 (HO1)
/ESC4/HO2: R72.1, U9.16 (HO2)
/ESC4/HO3: R77.1, U9.13 (HO3)
/ESC4/LO1: R68.1, U9.11 (LO1)
/ESC4/LO2: R73.1, U9.10 (LO2)
/ESC4/LO3: R78.1, U9.9 (LO3)
/ESC4/SWDCLK: TP7.1, U8.22 (PA14); also elsewhere on the board
/ESC4/SWDIO: TP8.1, U8.21 (PA13); also elsewhere on the board
/dshot_4: R66.1; also elsewhere on the board
GND: C43.2, C45.2, C46.2, C56.2, Q20.S, Q22.S, Q24.S, R31.1, R36.1, R49.1, R65.1, U8.16 (VSS), U8.29 (VSS), U9.6 (COM), U9.25 (COM); also elsewhere on the board
unnamed: Q19.G, R67.2
unnamed: Q20.G, R68.2
unnamed: Q21.G, R72.2
unnamed: Q22.G, R73.2
unnamed: Q23.G, R77.2
unnamed: Q24.G, R78.2
unnamed: R65.2, U8.1 (BOOT0)
unnamed: C45.1, U8.4 (NRST)
unnamed: R66.2, U8.25 (PB4)
unnamed: C55.2, U9.20 (VB1)
unnamed: C54.2, U9.17 (VB2)
unnamed: C53.2, U9.14 (VB3)

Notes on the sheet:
High Output
Bulk Decoupling
MCU
High Input
Back EMF
Place close to chip
Mosfets
Low Output
Mosfet Gate Driver
Low Input
